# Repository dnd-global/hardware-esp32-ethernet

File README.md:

# Module ESP32 Ethernet UART TTL công nghiệp

Module nối một thiết bị có cổng UART TTL 3,3 V vào mạng. Tín hiệu UART đi qua tầng cách ly 5 kV, rồi ESP32-S3 đưa dữ liệu lên mạng bằng Ethernet hoặc Wi-Fi. Mạch chạy nguồn 9–36 V.

**Tình trạng: Rev B, chưa sản xuất.** Mạch đã đi dây xong, qua kiểm tra luật thiết kế của KiCad và sắp đặt 5 mạch thử. Mọi thứ trong kho này chưa được kiểm chứng trên mạch thật.

| | |
|---|---|
| Kích thước | 80 × 66 mm, 2 lớp, dày 1,6 mm, đồng 1 oz |
| Nguồn vào | 9–36 V qua cọc vít, hạ áp bằng LMR36520 xuống 3,3 V |
| Vi điều khiển | ESP32-S3-WROOM-1-N8, anten mạch in |
| Ethernet | W5500 nối qua SPI, cổng RJ45 HR911105A có sẵn biến áp |
| UART | TTL 3,3 V, cách ly 5 kV bằng CA-IS3642HVW, khe cách ly trên mạch 7,6 mm |
| Đèn báo | LED nguồn và LED trạng thái RGB WS2812B-2020 trên IO38 |
| Linh kiện | 74 linh kiện, 43 loại, lắp một mặt |
| Phần mềm | KiCad 9 |

## Cần góp ý ở đâu

Rất mong nhận góp ý qua mục Issues, nhất là ở bốn chỗ:

1. Mạch hạ áp và lọc đầu vào: vị trí tụ, vòng dòng, tản nhiệt.
2. Đi dây Ethernet trên mạch 2 lớp: hai cặp TX, RX, thạch anh, lớp mass bên dưới.
3. Vùng cách ly: khoảng cách và linh kiện hai phía.
4. Vùng anten của ESP32: vùng cấm đồng, lỗ vít gần anten.

## Trong kho có gì

| Thư mục | Nội dung |
|---|---|
| [`kicad/`](kicad) | Dự án KiCad 9: mạch in, sơ đồ nguyên lý 5 trang, thư viện ký hiệu và footprint |
| [`fab/`](fab) | File đặt sản xuất: Gerber và file khoan, danh sách linh kiện, vị trí linh kiện |
| [`docs/`](docs) | Sơ đồ nguyên lý bản PDF và ảnh |
| [`tools/`](tools) | Bảng nối dây, công cụ sinh sơ đồ và đối chiếu với mạch in, công cụ kiểm tra file lắp ráp |

Mở dự án bằng file `kicad/esp32-eth-uart-module.kicad_pro`. Kho không kèm mô hình 3D của linh kiện nên trình xem 3D của KiCad chỉ hiện bo mạch trống.

## Sơ đồ khối

## Sơ đồ nguyên lý

Bản PDF đủ 5 trang: [`docs/so-do-nguyen-ly.pdf`](docs/so-do-nguyen-ly.pdf). Bấm vào từng ảnh để xem cỡ lớn.

| Trang | Ảnh |
|---|---|
| Nguồn 9–36 V sang 3,3 V |  |
| Vi điều khiển ESP32-S3 |  |
| Ethernet W5500 |  |
| UART TTL cách ly |  |

Mạch này được làm theo thứ tự ngược với thông thường: linh kiện được đặt bằng script từ bảng nối dây [`tools/netlist.py`](tools/netlist.py), đi dây tự động rồi chỉnh tiếp. Sơ đồ nguyên lý được sinh sau, cũng từ bảng đó, để người xem dễ đọc. Vì vậy **file mạch in là bản gốc**. Đừng chạy "Update PCB from Schematic": sáu pad đo mang tên khác nhau ở hai bên (TP1–TP6 trong sơ đồ, 3V3/GND/TXD/RXD/VISO/GISO trên mạch) và footprint trên mạch chưa gắn với ký hiệu trong sơ đồ.

Sơ đồ được đối chiếu tự động với mạch in bằng [`tools/schematic/check_sch.py`](tools/schematic/check_sch.py): 81 linh kiện, 53 đường mạch và 256 chân đều khớp, tên đường mạch cũng trùng. Kiểm tra luật điện (ERC) của KiCad không báo lỗi.

## Mạch in

Vùng sẫm hình chữ L bên phải là khe cách ly. Sáu chấm vàng là pad đo. Hàng lỗ J5 ở mép dưới để trống, dùng khi nạp chương trình.

| Lớp trên | Lớp dưới |
|---|---|
|  |  |

Cận cảnh ba vùng đáng xem kỹ. Trong các ảnh này, đỏ là lớp trên, xanh dương là lớp dưới, chữ trắng là tên đường mạch, nét đứt vàng là vùng cấm đồng.

| Nguồn | Ethernet | Vùng cách ly |
|---|---|---|
|  |  |  |

Ảnh 3D khác: [nhìn chéo phía sau](docs/img/3d-cheo-sau.jpg), [mặt dưới](docs/img/3d-mat-duoi.jpg). Ảnh 3D do KiCad dựng từ mô hình linh kiện, không phải ảnh chụp mạch thật.

## Thông số chế tạo

| | |
|---|---|
| Mạch | 2 lớp, 80 × 66 mm, dày 1,6 mm, đồng 1 oz |
| Đường mạch | nhỏ nhất 0,2 mm, khe hở nhỏ nhất 0,15 mm |
| Via | 0,6 mm, lỗ 0,3 mm, phủ sơn |
| Lỗ bắt vít | 4 lỗ M3 (3,2 mm), không mạ |
| Lắp ráp | 74 linh kiện, một mặt. Cổng RJ45 và cọc vít là loại cắm xuyên lỗ. Hàng chân J5 không lắp. |

File trong `fab/` được chuẩn bị cho dịch vụ lắp ráp của JLCPCB:

- `gateway-s3-revb-gerber.zip`: 9 lớp Gerber và 2 file khoan.
- `gateway-s3-revb-bom.csv`: danh sách linh kiện kèm mã LCSC, mỗi mã một dòng.
- `gateway-s3-revb-cpl.csv`: vị trí và góc đặt linh kiện.

JLCPCB đặt footprint trong thư viện của họ vào vị trí và góc ghi ở file CPL, nên chỗ nào footprint KiCad khác footprint JLCPCB thì file CPL phải bù lại. Ở mạch này có bốn chỗ: U5 xoay −90°, D3 xoay 180°, U4 xoay 270°, J6 lệch 1,41 mm. [`tools/fab/check_cpl.py`](tools/fab/check_cpl.py) kiểm tra việc này cho cả 74 linh kiện: nó đặt footprint của JLCPCB theo từng dòng CPL rồi đo xem mỗi chân rơi cách pad trên mạch bao xa và có đúng chân không.

## Hạn chế đã biết

- Mạch 2 lớp nên hai cặp Ethernet không kiểm soát được trở kháng. Bù lại, đường ngắn dưới 25 mm và không qua via.
- Lớp mass mặt dưới bị một số đường tín hiệu chậm cắt qua, có đoạn nằm dưới W5500.
- Cổng RJ45 chỉ ghi chịu 0–70 °C, cổng USB-C từ −30 đến 80 °C; chưa phải dải nhiệt công nghiệp đầy đủ.
- Vỏ cổng RJ45 nối thẳng mass, không qua tụ 1 nF / 2 kV. Chưa có linh kiện chống tĩnh điện riêng cho cặp Ethernet.
- Đầu cắm UART mượn đầu USB-C nhưng không phải cổng USB: D− là chiều phát ra thiết bị ngoài, D+ là chiều thu về, mức 3,3 V.
- LED trạng thái WS2812B-2020-V6 chạy ở 3,3 V, đúng mép dưới dải cấp 3,3–5,3 V của nó. Độ sáng trong datasheet đo ở 5 V nên trên mạch này có thể thấp hơn.

## Công cụ

Cần KiCad 9 (lệnh `kicad-cli` và module Python `pcbnew`).

```sh
# sinh lại sơ đồ từ bảng nối dây, đối chiếu với mạch in, chạy ERC, xuất PDF và SVG vào tools/schematic/out
cd tools/schematic && ./build.sh

# xuất lại Gerber, danh sách linh kiện và file vị trí vào fab/, rồi kiểm tra file vị trí
cd tools/fab && ./fab.sh && python3 check_cpl.py
```

`check_cpl.py` tải dữ liệu footprint của từng mã LCSC từ thư viện JLCEDA/EasyEDA ở lần chạy đầu và lưu vào `tools/fab/jlc-lib/`.

## Nguồn tham khảo

- Một số footprint trong `kicad/lcsc.pretty` được chuyển từ thư viện chính thức JLCEDA/EasyEDA.
- Mạch đầu cuối Ethernet theo sơ đồ mẫu của WIZnet cho W5500 dùng cổng RJ45 có sẵn biến áp.

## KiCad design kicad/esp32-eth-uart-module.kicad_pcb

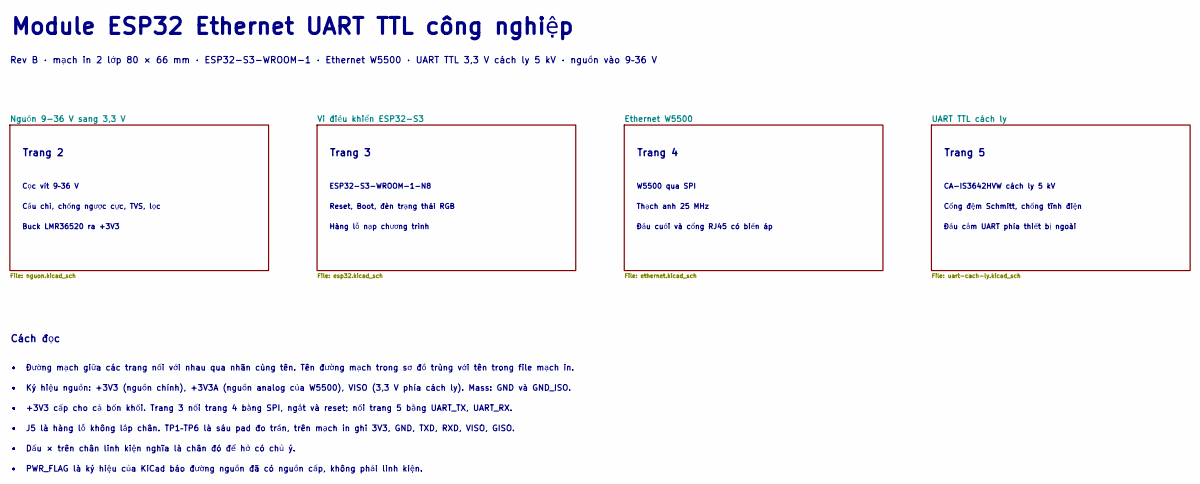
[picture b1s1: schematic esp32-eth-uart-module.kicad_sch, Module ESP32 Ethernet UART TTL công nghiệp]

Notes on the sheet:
Module ESP32 Ethernet UART TTL công nghiệp
Rev B · mạch in 2 lớp 80 × 66 mm · ESP32-S3-WROOM-1 · Ethernet W5500 · UART TTL 3,3 V cách ly 5 kV · nguồn vào 9–36 V
Trang 2
Cọc vít 9–36 V
Cầu chì, chống ngược cực, TVS, lọc
Buck LMR36520 ra +3V3
Trang 3
ESP32-S3-WROOM-1-N8
Reset, Boot, đèn trạng thái RGB
Hàng lỗ nạp chương trình
Trang 4
W5500 qua SPI
Thạch anh 25 MHz
Đầu cuối và cổng RJ45 có biến áp
Trang 5
CA-IS3642HVW cách ly 5 kV
Cổng đệm Schmitt, chống tĩnh điện
Đầu cắm UART phía thiết bị ngoài
Cách đọc
• Đường mạch giữa các trang nối với nhau qua nhãn cùng tên. Tên đường mạch trong sơ đồ trùng với tên trong file mạch in.
• Ký hiệu nguồn: +3V3 (nguồn chính), +3V3A (nguồn analog của W5500), VISO (3,3 V phía cách ly). Mass: GND và GND_ISO.
• +3V3 cấp cho cả bốn khối. Trang 3 nối trang 4 bằng SPI, ngắt và reset; nối trang 5 bằng UART_TX, UART_RX.
• J5 là hàng lỗ không lắp chân. TP1–TP6 là sáu pad đo trần, trên mạch in ghi 3V3, GND, TXD, RXD, VISO, GISO.
• Dấu × trên chân linh kiện nghĩa là chân đó để hở có chủ ý.
• PWR_FLAG là ký hiệu của KiCad báo đường nguồn đã có nguồn cấp, không phải linh kiện.

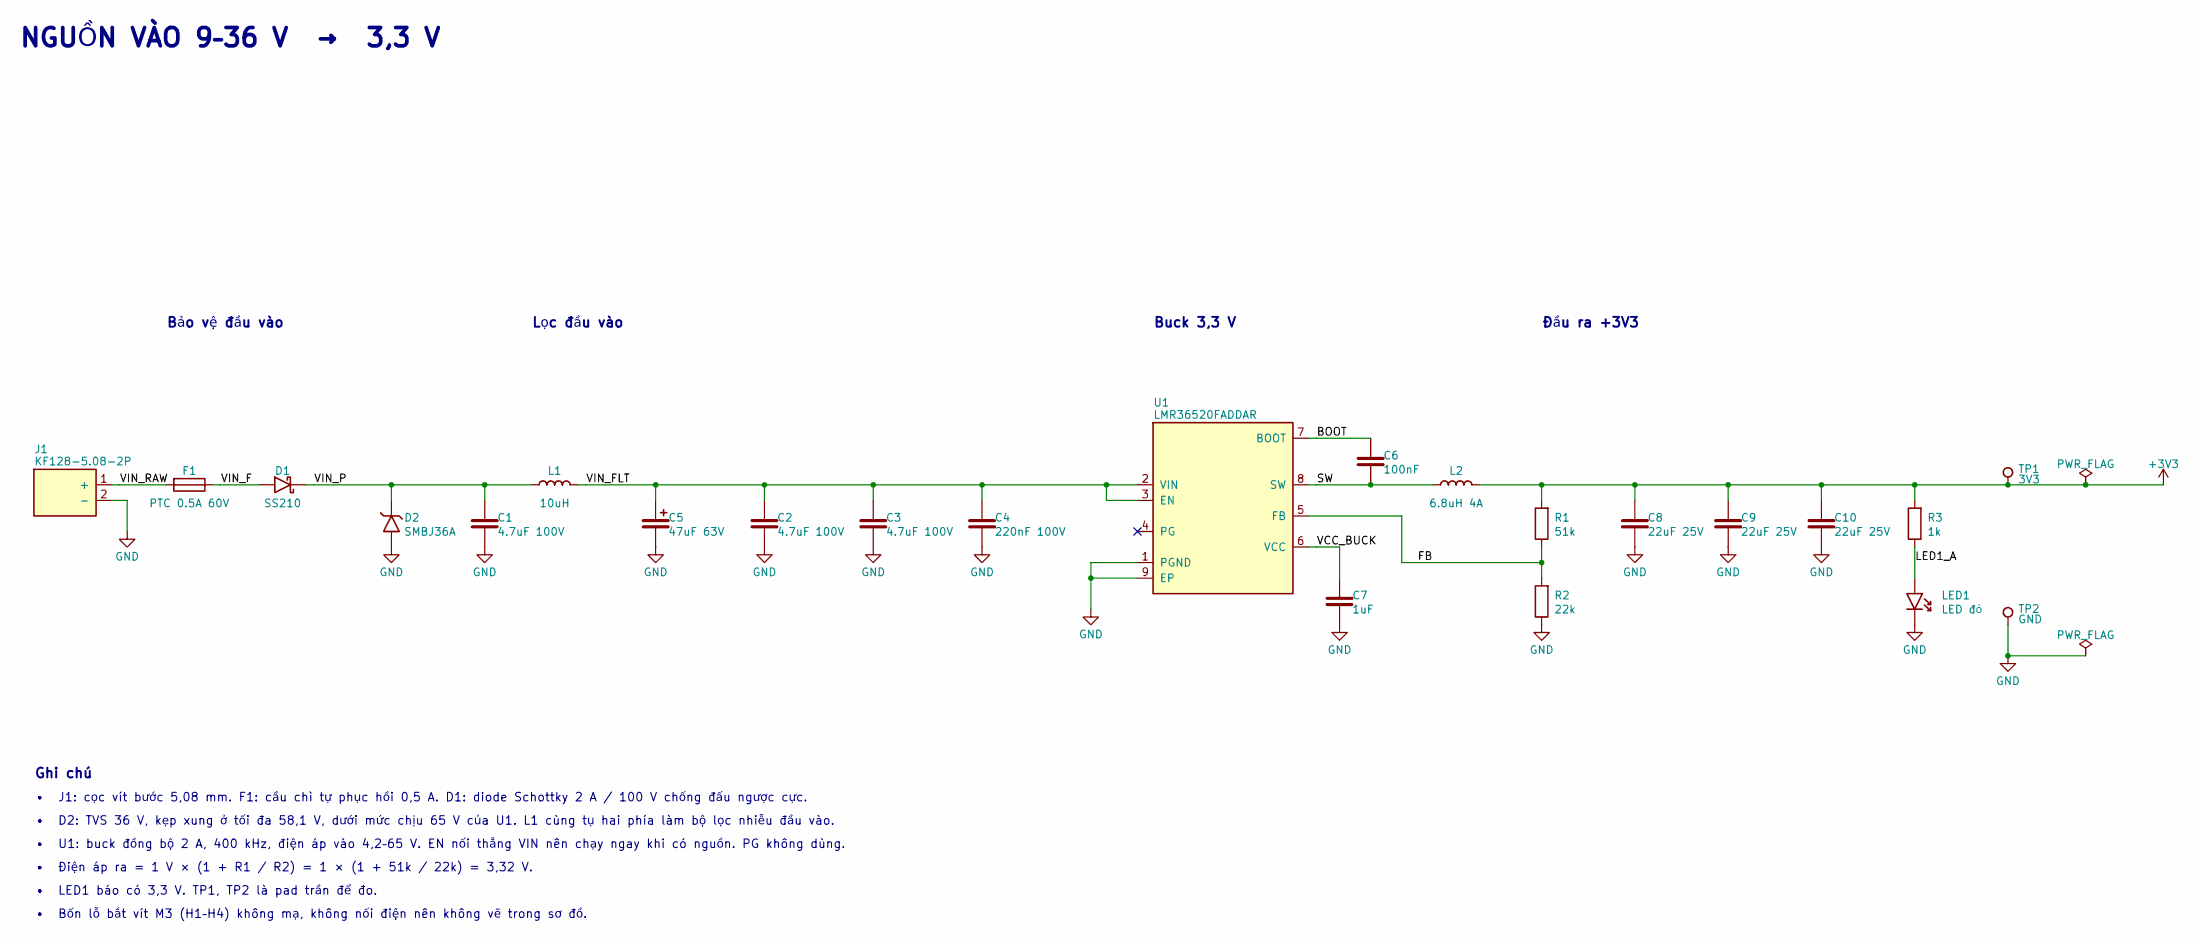
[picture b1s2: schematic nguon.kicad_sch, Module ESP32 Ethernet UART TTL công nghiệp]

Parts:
C1, C2, C3: 4.7uF 100V; C_1210_3225Metric; LCSC C381466
C4: 220nF 100V; C_0603_1608Metric; LCSC C36911431
C5: 47uF 63V; CP_Elec_6.3x7.7; LCSC C48971005
C6: 100nF; C_0603_1608Metric; LCSC C14663
C7: 1uF; C_0603_1608Metric; LCSC C15849
C8, C9, C10: 22uF 25V; C_1206_3216Metric; LCSC C12891
D1: SS210; D_SMA; LCSC C14996
D2: SMBJ36A; D_SMB; LCSC C353364
F1: PTC 0.5A 60V; F1812; LCSC C70113
J1: KF128-5.08-2P; CONN-TH_2P-P5.08_KF128-5.08-2P; LCSC C474952
L1: 10uH; IND-SMD_L4.0-W4.0; LCSC C38117
L2: 6.8uH 4A; IND-SMD_L7.0-W6.6; LCSC C357230
LED1: LED đỏ; LED_0603_1608Metric; LCSC C2286
R1: 51k; R_0603_1608Metric; LCSC C23196
R2: 22k; R_0603_1608Metric; LCSC C31850
R3: 1k; R_0603_1608Metric; LCSC C21190
TP1: 3V3; TestPoint_Pad_D1.5mm
TP2: GND; TestPoint_Pad_D1.5mm
U1: LMR36520FADDAR; POWERPAD-SO-8_L4.9-W3.9-P1.27-LS6.0-BL-EP; LCSC C1858395

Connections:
+3V3: C8.1, C9.1, C10.1, L2.2, R1.1, R3.1, TP1.1; also elsewhere on the board
BOOT: C6.1, U1.7 (BOOT)
FB: R1.2, R2.1, U1.5 (FB)
GND: C1.2, C2.2, C3.2, C4.2, C5.2, C7.2, C8.2, C9.2, C10.2, D2.2, J1.2 (-), LED1.1, R2.2, TP2.1, U1.1 (PGND), U1.9 (EP); also elsewhere on the board
LED1_A: LED1.2, R3.2
PG: U1.4 (PG)
SW: C6.2, L2.1, U1.8 (SW)
VCC_BUCK: C7.1, U1.6 (VCC)
VIN_F: D1.2, F1.1
VIN_FLT: C2.1, C3.1, C4.1, C5.1, L1.2, U1.2 (VIN), U1.3 (EN)
VIN_P: C1.1, D1.1, D2.1, L1.1
VIN_RAW: F1.2, J1.1 (+)

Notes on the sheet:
NGUỒN VÀO 9–36 V → 3,3 V
Bảo vệ đầu vào
Lọc đầu vào
Buck 3,3 V
Đầu ra +3V3
Ghi chú
• J1: cọc vít bước 5,08 mm. F1: cầu chì tự phục hồi 0,5 A. D1: diode Schottky 2 A / 100 V chống đấu ngược cực.
• D2: TVS 36 V, kẹp xung ở tối đa 58,1 V, dưới mức chịu 65 V của U1. L1 cùng tụ hai phía làm bộ lọc nhiễu đầu vào.
• U1: buck đồng bộ 2 A, 400 kHz, điện áp vào 4,2–65 V. EN nối thẳng VIN nên chạy ngay khi có nguồn. PG không dùng.
• Điện áp ra = 1 V × (1 + R1 / R2) = 1 × (1 + 51k / 22k) = 3,32 V.
• LED1 báo có 3,3 V. TP1, TP2 là pad trần để đo.
• Bốn lỗ bắt vít M3 (H1–H4) không mạ, không nối điện nên không vẽ trong sơ đồ.

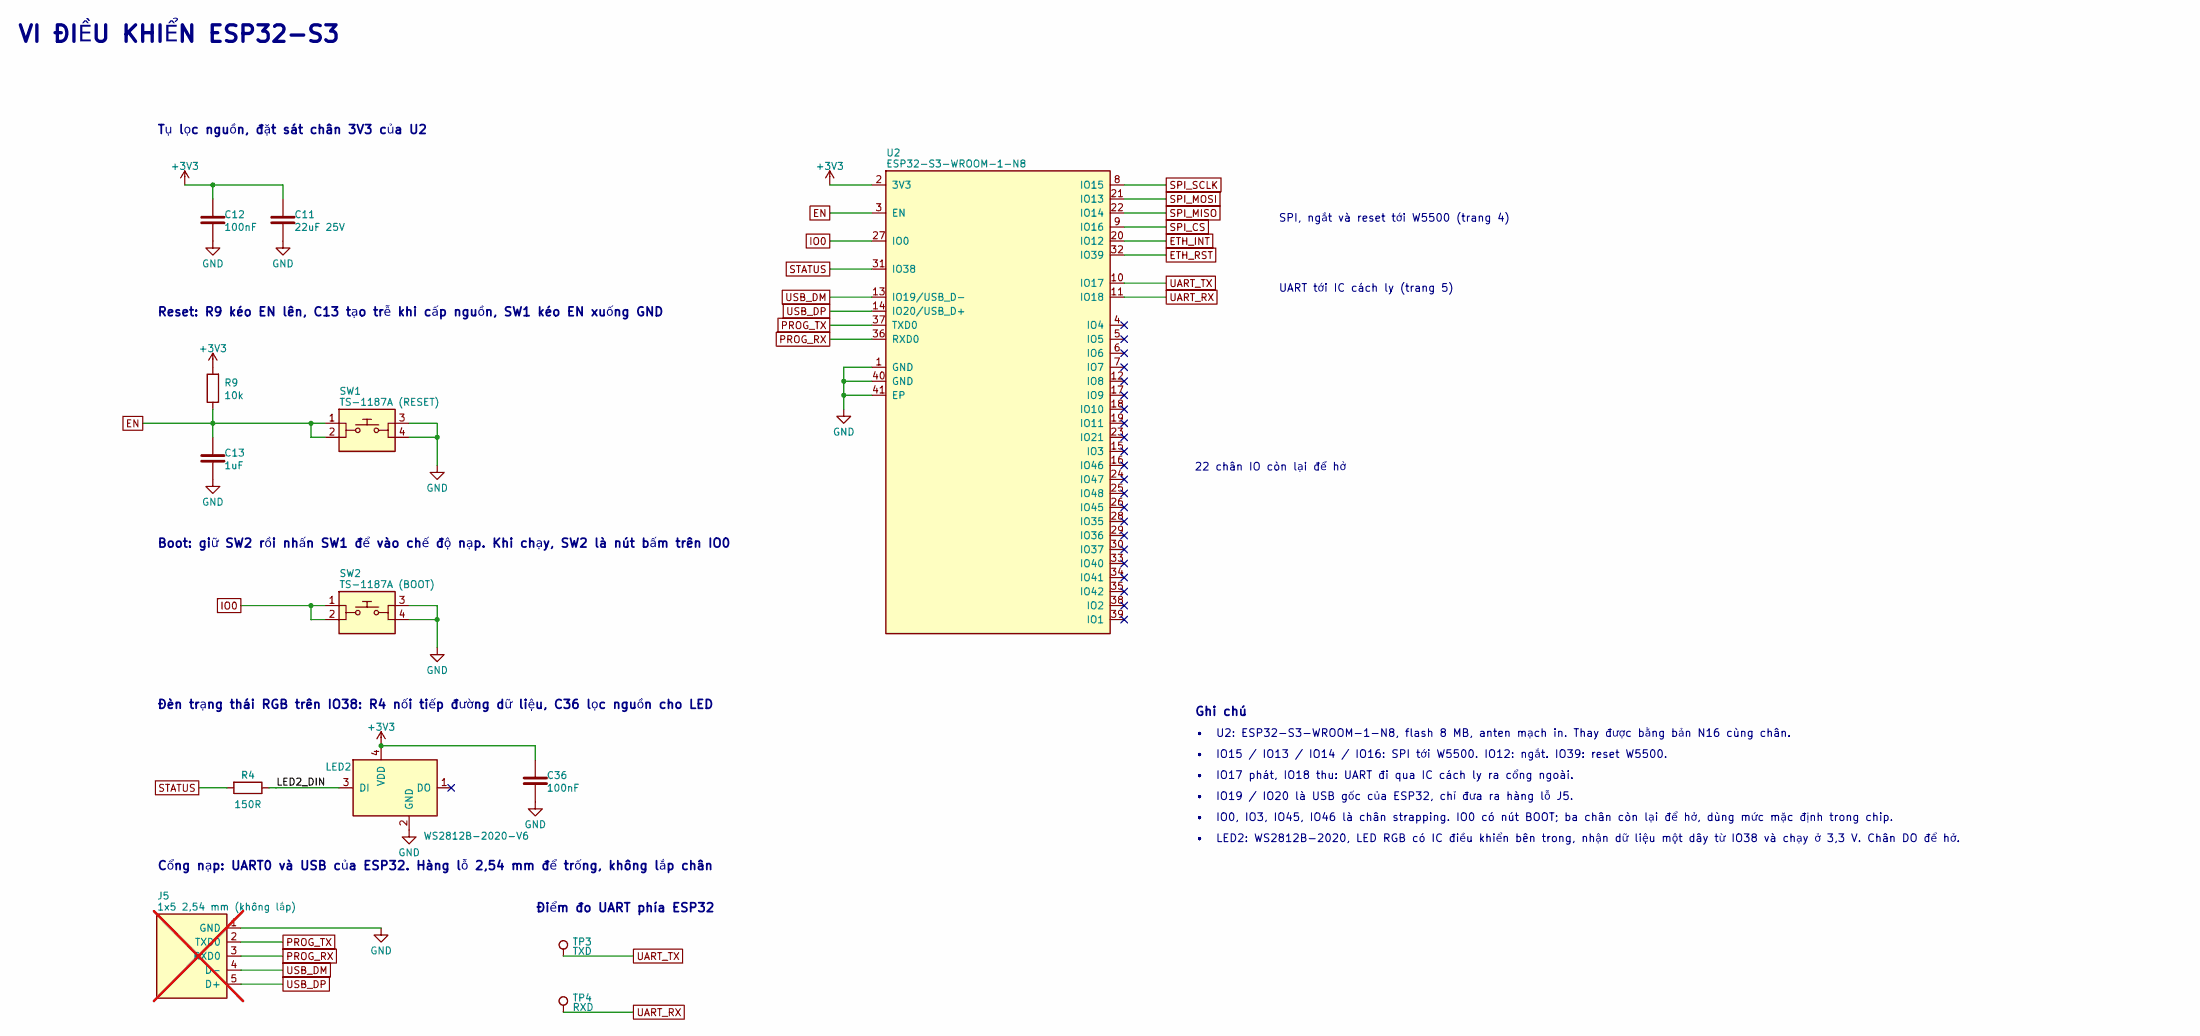
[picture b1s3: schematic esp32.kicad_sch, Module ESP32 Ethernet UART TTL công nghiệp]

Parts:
C11: 22uF 25V; C_1206_3216Metric; LCSC C12891
C12, C36: 100nF; C_0603_1608Metric; LCSC C14663
C13: 1uF; C_0603_1608Metric; LCSC C15849
J5: 1x5 2,54 mm (không lắp); PinHeader_1x05_P2.54mm_Vertical; not fitted
LED2: WS2812B-2020-V6; LED_WS2812B-2020_PLCC4_2.0x2.0mm; LCSC C52917434
R4: 150R; R_0603_1608Metric; LCSC C22808
R9: 10k; R_0603_1608Metric; LCSC C25804
SW1: TS-1187A (RESET); SW-SMD_4P-L5.1-W5.1-P3.70-LS6.5-TL_H1.5; LCSC C318884
SW2: TS-1187A (BOOT); SW-SMD_4P-L5.1-W5.1-P3.70-LS6.5-TL_H1.5; LCSC C318884
TP3: TXD; TestPoint_Pad_D1.5mm
TP4: RXD; TestPoint_Pad_D1.5mm
U2: ESP32-S3-WROOM-1-N8; WIFIM-SMD_ESP32-S3-WROOM-1-N8; LCSC C2913198

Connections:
+3V3: C11.1, C12.1, C36.1, LED2.4 (VDD), R9.1, U2.2 (3V3); also elsewhere on the board
EN: C13.1, R9.2, SW1.1, SW1.2, U2.3 (EN)
ETH_INT: U2.20 (IO12); also elsewhere on the board
ETH_RST: U2.32 (IO39); also elsewhere on the board
GND: C11.2, C12.2, C13.2, C36.2, J5.1 (GND), LED2.2 (GND), SW1.3, SW1.4, SW2.3, SW2.4, U2.1 (GND), U2.40 (GND), U2.41 (EP); also elsewhere on the board
IO0: SW2.1, SW2.2, U2.27 (IO0)
LED2_DIN: LED2.3 (DI), R4.2
PROG_RX: J5.3 (RXD0), U2.36 (RXD0)
PROG_TX: J5.2 (TXD0), U2.37 (TXD0)
SPI_CS: U2.9 (IO16); also elsewhere on the board
SPI_MISO: U2.22 (IO14); also elsewhere on the board
SPI_MOSI: U2.21 (IO13); also elsewhere on the board
SPI_SCLK: U2.8 (IO15); also elsewhere on the board
STATUS: R4.1, U2.31 (IO38)
UART_RX: TP4.1, U2.11 (IO18); also elsewhere on the board
UART_TX: TP3.1, U2.10 (IO17); also elsewhere on the board
USB_DM: J5.4 (D-), U2.13 (IO19/USB_D-)
USB_DP: J5.5 (D+), U2.14 (IO20/USB_D+)

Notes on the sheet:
VI ĐIỀU KHIỂN ESP32-S3
SPI, ngắt và reset tới W5500 (trang 4)
UART tới IC cách ly (trang 5)
22 chân IO còn lại để hở
Tụ lọc nguồn, đặt sát chân 3V3 của U2
Reset: R9 kéo EN lên, C13 tạo trễ khi cấp nguồn, SW1 kéo EN xuống GND
Boot: giữ SW2 rồi nhấn SW1 để vào chế độ nạp. Khi chạy, SW2 là nút bấm trên IO0
Đèn trạng thái RGB trên IO38: R4 nối tiếp đường dữ liệu, C36 lọc nguồn cho LED
Cổng nạp: UART0 và USB của ESP32. Hàng lỗ 2,54 mm để trống, không lắp chân
Điểm đo UART phía ESP32
Ghi chú
• U2: ESP32-S3-WROOM-1-N8, flash 8 MB, anten mạch in. Thay được bằng bản N16 cùng chân.
• IO15 / IO13 / IO14 / IO16: SPI tới W5500. IO12: ngắt. IO39: reset W5500.
• IO17 phát, IO18 thu: UART đi qua IC cách ly ra cổng ngoài.
• IO19 / IO20 là USB gốc của ESP32, chỉ đưa ra hàng lỗ J5.
• IO0, IO3, IO45, IO46 là chân strapping. IO0 có nút BOOT; ba chân còn lại để hở, dùng mức mặc định trong chip.
• LED2: WS2812B-2020, LED RGB có IC điều khiển bên trong, nhận dữ liệu một dây từ IO38 và chạy ở 3,3 V. Chân DO để hở.

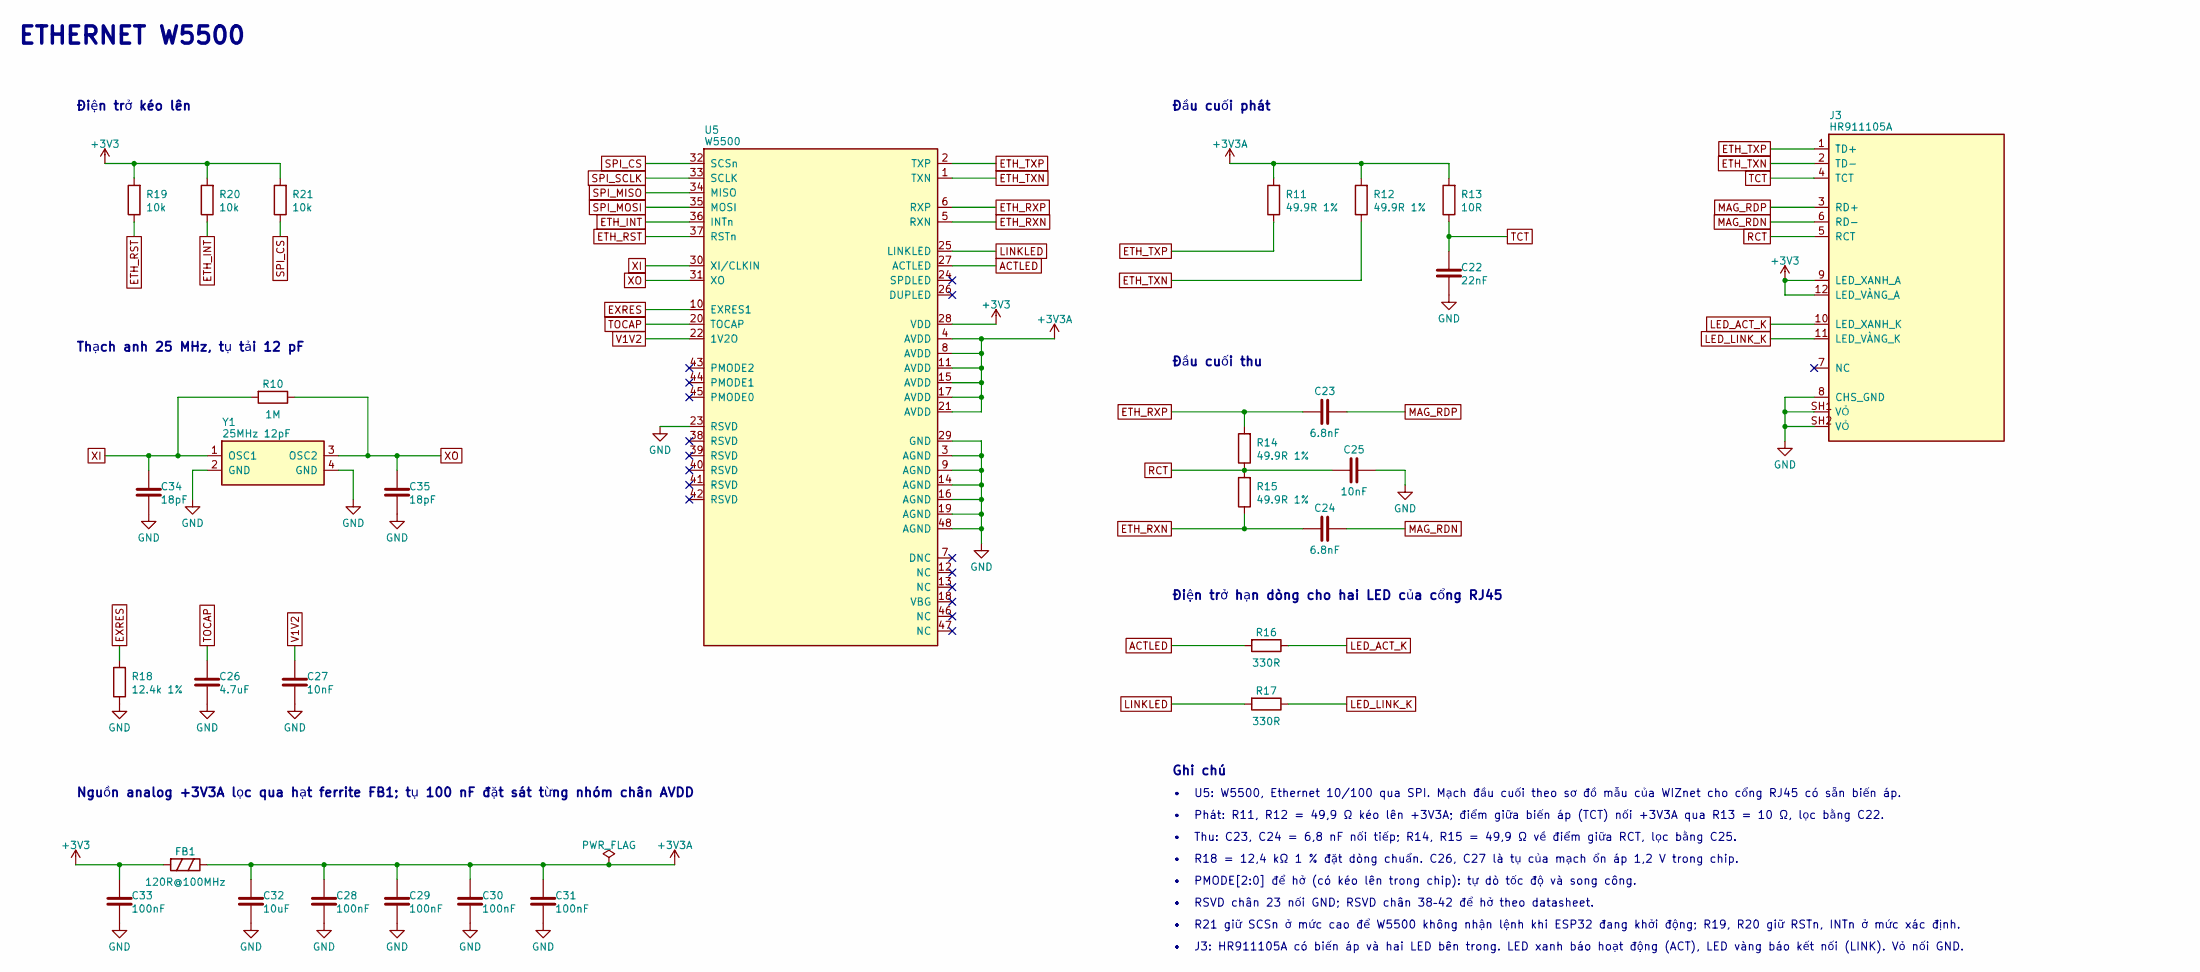
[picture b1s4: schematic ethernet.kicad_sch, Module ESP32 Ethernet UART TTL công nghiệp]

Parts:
C22: 22nF; C_0603_1608Metric; LCSC C21122
C23, C24: 6.8nF; C_0603_1608Metric; LCSC C1631
C25, C27: 10nF; C_0603_1608Metric; LCSC C57112
C26: 4.7uF; C_0603_1608Metric; LCSC C19666
C28, C29, C30, C31, C33: 100nF; C_0603_1608Metric; LCSC C14663
C32: 10uF; C_0805_2012Metric; LCSC C15850
C34, C35: 18pF; C_0603_1608Metric; LCSC C1647
FB1: 120R@100MHz; L_0603_1608Metric; LCSC C14709
J3: HR911105A; RJ45-TH_HR911105A; LCSC C12074
R10: 1M; R_0603_1608Metric; LCSC C22935
R11, R12, R14, R15: 49.9R 1%; R_0603_1608Metric; LCSC C23185
R13: 10R; R_0603_1608Metric; LCSC C22859
R16, R17: 330R; R_0603_1608Metric; LCSC C23138
R18: 12.4k 1%; R_0603_1608Metric; LCSC C2930060
R19, R20, R21: 10k; R_0603_1608Metric; LCSC C25804
U5: W5500; LQFP-48_7x7mm_P0.5mm; LCSC C32843
Y1: 25MHz 12pF; Crystal_SMD_3225-4Pin_3.2x2.5mm; LCSC C9006

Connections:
+3V3: C33.1, FB1.1, J3.9 (LED_XANH_A), J3.12 (LED_VÀNG_A), R19.1, R20.1, R21.1, U5.28 (VDD); also elsewhere on the board
+3V3A: C28.1, C29.1, C30.1, C31.1, C32.1, FB1.2, R11.1, R12.1, R13.1, U5.4 (AVDD), U5.8 (AVDD), U5.11 (AVDD), U5.15 (AVDD), U5.17 (AVDD), U5.21 (AVDD)
ACTLED: R16.2, U5.27 (ACTLED)
ETH_INT: R20.2, U5.36 (INTn); also elsewhere on the board
ETH_RST: R19.2, U5.37 (RSTn); also elsewhere on the board
ETH_RXN: C24.1, R15.1, U5.5 (RXN)
ETH_RXP: C23.1, R14.1, U5.6 (RXP)
ETH_TXN: J3.2 (TD-), R12.2, U5.1 (TXN)
ETH_TXP: J3.1 (TD+), R11.2, U5.2 (TXP)
EXRES: R18.1, U5.10 (EXRES1)
GND: C22.2, C25.2, C26.2, C27.2, C28.2, C29.2, C30.2, C31.2, C32.2, C33.2, C34.2, C35.2, J3.8 (CHS_GND), J3.SH1 (VỎ), J3.SH2 (VỎ), R18.2, U5.3 (AGND), U5.9 (AGND), U5.14 (AGND), U5.16 (AGND), U5.19 (AGND), U5.23 (RSVD), U5.29 (GND), U5.48 (AGND), Y1.2 (GND), Y1.4 (GND); also elsewhere on the board
LED_ACT_K: J3.10 (LED_XANH_K), R16.1
LED_LINK_K: J3.11 (LED_VÀNG_K), R17.1
LINKLED: R17.2, U5.25 (LINKLED)
MAG_RDN: C24.2, J3.6 (RD-)
MAG_RDP: C23.2, J3.3 (RD+)
RCT: C25.1, J3.5 (RCT), R14.2, R15.2
SPI_CS: R21.2, U5.32 (SCSn); also elsewhere on the board
SPI_MISO: U5.34 (MISO); also elsewhere on the board
SPI_MOSI: U5.35 (MOSI); also elsewhere on the board
SPI_SCLK: U5.33 (SCLK); also elsewhere on the board
TCT: C22.1, J3.4 (TCT), R13.2
TOCAP: C26.1, U5.20 (TOCAP)
V1V2: C27.1, U5.22 (1V2O)
XI: C34.1, R10.1, U5.30 (XI/CLKIN), Y1.1 (OSC1)
XO: C35.1, R10.2, U5.31 (XO), Y1.3 (OSC2)

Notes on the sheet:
ETHERNET W5500
Điện trở kéo lên
Thạch anh 25 MHz, tụ tải 12 pF
Nguồn analog +3V3A lọc qua hạt ferrite FB1; tụ 100 nF đặt sát từng nhóm chân AVDD
Đầu cuối phát
Đầu cuối thu
Điện trở hạn dòng cho hai LED của cổng RJ45
Ghi chú
• U5: W5500, Ethernet 10/100 qua SPI. Mạch đầu cuối theo sơ đồ mẫu của WIZnet cho cổng RJ45 có sẵn biến áp.
• Phát: R11, R12 = 49,9 Ω kéo lên +3V3A; điểm giữa biến áp (TCT) nối +3V3A qua R13 = 10 Ω, lọc bằng C22.
• Thu: C23, C24 = 6,8 nF nối tiếp; R14, R15 = 49,9 Ω về điểm giữa RCT, lọc bằng C25.
• R18 = 12,4 kΩ 1 % đặt dòng chuẩn. C26, C27 là tụ của mạch ổn áp 1,2 V trong chip.
• PMODE[2:0] để hở (có kéo lên trong chip): tự dò tốc độ và song công.
• RSVD chân 23 nối GND; RSVD chân 38–42 để hở theo datasheet.
• R21 giữ SCSn ở mức cao để W5500 không nhận lệnh khi ESP32 đang khởi động; R19, R20 giữ RSTn, INTn ở mức xác định.
• J3: HR911105A có biến áp và hai LED bên trong. LED xanh báo hoạt động (ACT), LED vàng báo kết nối (LINK). Vỏ nối GND.

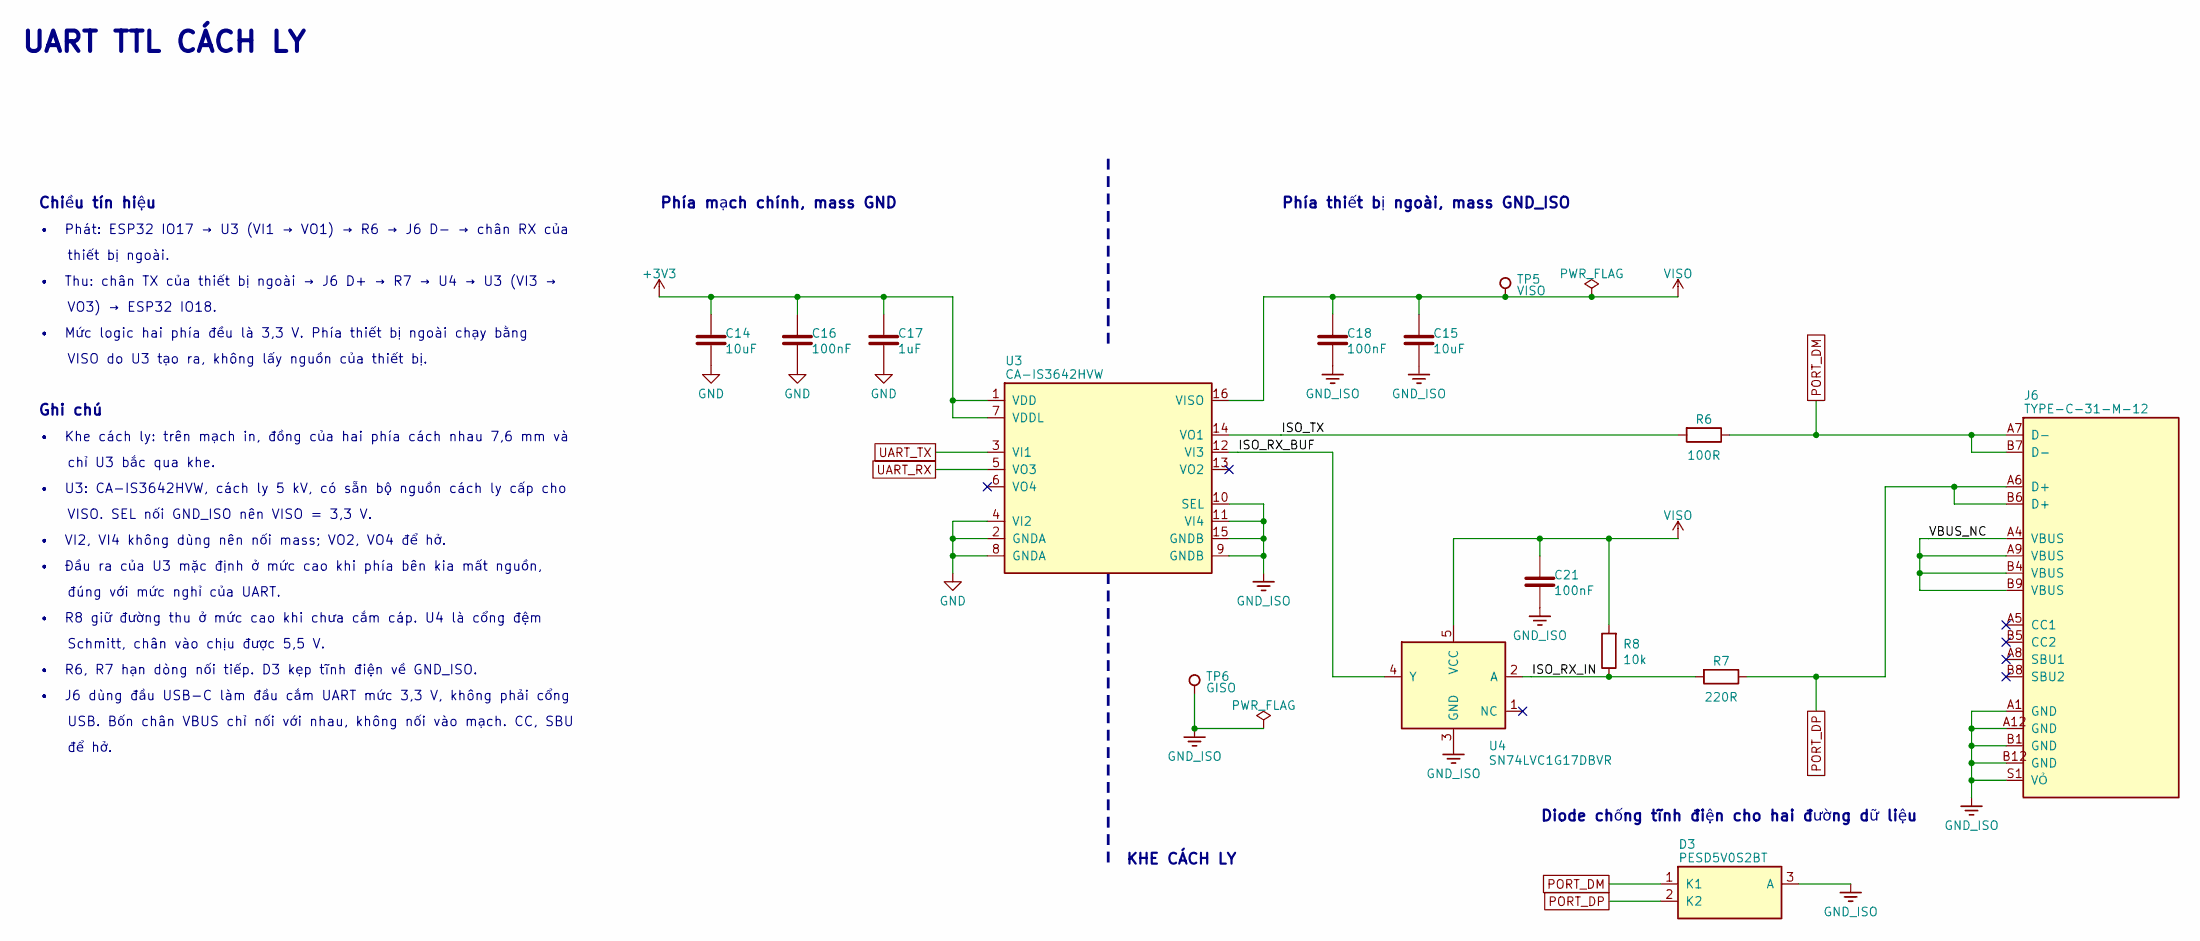
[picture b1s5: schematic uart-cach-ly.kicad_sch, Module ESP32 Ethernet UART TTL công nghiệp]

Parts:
C14, C15: 10uF; C_0805_2012Metric; LCSC C15850
C16, C18, C21: 100nF; C_0603_1608Metric; LCSC C14663
C17: 1uF; C_0603_1608Metric; LCSC C15849
D3: PESD5V0S2BT; SOT-23; LCSC C49338
J6: TYPE-C-31-M-12; USB_C_Receptacle_HRO_TYPE-C-31-M-12; LCSC C165948
R6: 100R; R_0603_1608Metric; LCSC C22775
R7: 220R; R_0603_1608Metric; LCSC C22962
R8: 10k; R_0603_1608Metric; LCSC C25804
TP5: VISO; TestPoint_Pad_D1.5mm
TP6: GISO; TestPoint_Pad_D1.5mm
U3: CA-IS3642HVW; SOIC-16_L10.3-W7.5-P1.27-LS10.3-TL; LCSC C5440874
U4: SN74LVC1G17DBVR; SOT-25-5_L3.0-W1.8-P0.95-LS3.0-BL; LCSC C7836

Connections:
+3V3: C14.1, C16.1, C17.1, U3.1 (VDD), U3.7 (VDDL); also elsewhere on the board
GND: C14.2, C16.2, C17.2, U3.2 (GNDA), U3.4 (VI2), U3.8 (GNDA); also elsewhere on the board
GND_ISO: C15.2, C18.2, C21.2, D3.3 (A), J6.A1 (GND), J6.A12 (GND), J6.B1 (GND), J6.B12 (GND), J6.S1 (VỎ), TP6.1, U3.9 (GNDB), U3.10 (SEL), U3.11 (VI4), U3.15 (GNDB), U4.3 (GND); also elsewhere on the board
ISO_RX_BUF: U3.12 (VI3), U4.4 (Y)
ISO_RX_IN: R7.2, R8.2, U4.2 (A)
ISO_TX: R6.1, U3.14 (VO1)
PORT_DM: D3.1 (K1), J6.A7 (D-), J6.B7 (D-), R6.2
PORT_DP: D3.2 (K2), J6.A6 (D+), J6.B6 (D+), R7.1
UART_RX: U3.5 (VO3); also elsewhere on the board
UART_TX: U3.3 (VI1); also elsewhere on the board
VBUS_NC: J6.A4 (VBUS), J6.A9 (VBUS), J6.B4 (VBUS), J6.B9 (VBUS)
VISO: C15.1, C18.1, C21.1, R8.1, TP5.1, U3.16 (VISO), U4.5 (VCC); also elsewhere on the board

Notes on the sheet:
UART TTL CÁCH LY
Diode chống tĩnh điện cho hai đường dữ liệu
KHE CÁCH LY
Phía mạch chính, mass GND
Phía thiết bị ngoài, mass GND_ISO
Chiều tín hiệu
• Phát: ESP32 IO17 → U3 (VI1 → VO1) → R6 → J6 D− → chân RX của
thiết bị ngoài.
• Thu: chân TX của thiết bị ngoài → J6 D+ → R7 → U4 → U3 (VI3 →
VO3) → ESP32 IO18.
• Mức logic hai phía đều là 3,3 V. Phía thiết bị ngoài chạy bằng
VISO do U3 tạo ra, không lấy nguồn của thiết bị.
Ghi chú
• Khe cách ly: trên mạch in, đồng của hai phía cách nhau 7,6 mm và
chỉ U3 bắc qua khe.
• U3: CA-IS3642HVW, cách ly 5 kV, có sẵn bộ nguồn cách ly cấp cho
VISO. SEL nối GND_ISO nên VISO = 3,3 V.
• VI2, VI4 không dùng nên nối mass; VO2, VO4 để hở.
• Đầu ra của U3 mặc định ở mức cao khi phía bên kia mất nguồn,
đúng với mức nghỉ của UART.
• R8 giữ đường thu ở mức cao khi chưa cắm cáp. U4 là cổng đệm
Schmitt, chân vào chịu được 5,5 V.
• R6, R7 hạn dòng nối tiếp. D3 kẹp tĩnh điện về GND_ISO.
• J6 dùng đầu USB-C làm đầu cắm UART mức 3,3 V, không phải cổng
USB. Bốn chân VBUS chỉ nối với nhau, không nối vào mạch. CC, SBU
để hở.

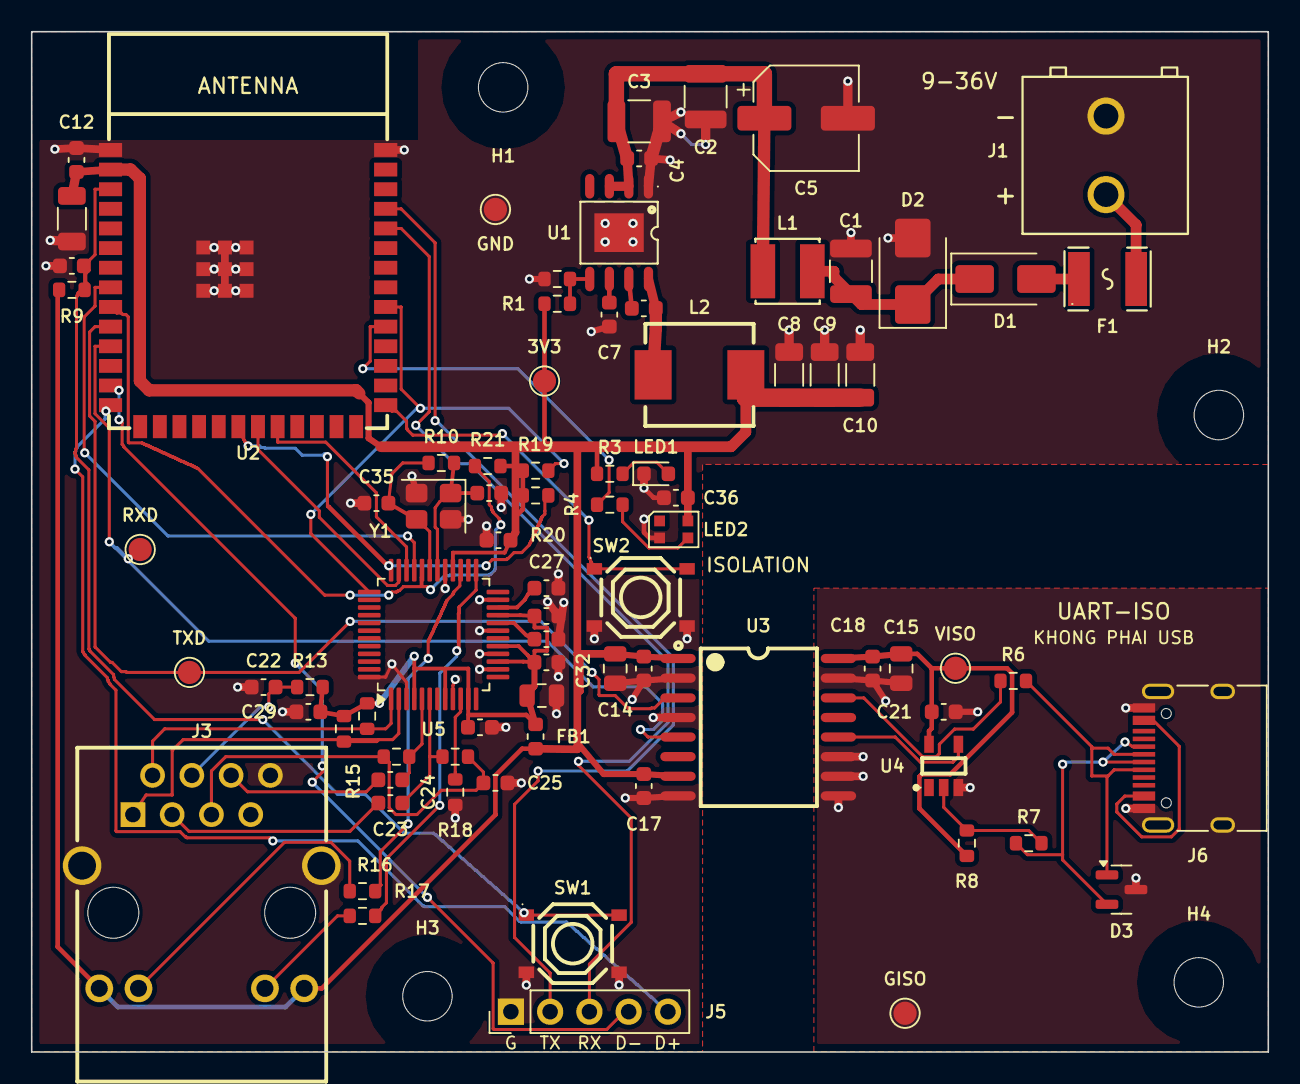
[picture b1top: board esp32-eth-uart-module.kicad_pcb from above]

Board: 2 copper layers, 80.0 x 66.0 mm, 85 parts (0 on the bottom side), 53 nets.

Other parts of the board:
3V3: test point +3V3; TestPoint_Pad_D1.5mm
GISO: test point GND_ISO; TestPoint_Pad_D1.5mm
GND: test point GND; TestPoint_Pad_D1.5mm
H1, H2, H3, H4: MountingHole_3.2mm_M3
RXD: test point UART_RX; TestPoint_Pad_D1.5mm
TXD: test point UART_TX; TestPoint_Pad_D1.5mm
VISO: test point VISO; TestPoint_Pad_D1.5mm

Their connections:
+3V3: 3V3.1; also elsewhere on the board
GND: GND.1; also elsewhere on the board
GND_ISO: GISO.1; also elsewhere on the board
UART_RX: RXD.1; also elsewhere on the board
UART_TX: TXD.1; also elsewhere on the board
VISO: VISO.1; also elsewhere on the board

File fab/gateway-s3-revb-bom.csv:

Comment,Designator,Footprint,LCSC Part #
4.7uF 100V,"C1,C2,C3",C_1210_3225Metric,C381466
22nF,C22,C_0603_1608Metric,C21122
6.8nF,"C23,C24",C_0603_1608Metric,C1631
4.7uF,C26,C_0603_1608Metric,C19666
10nF,"C27,C25",C_0603_1608Metric,C57112
10uF,"C32,C14,C15",C_0805_2012Metric,C15850
18pF,"C34,C35",C_0603_1608Metric,C1647
220nF 100V,C4,C_0603_1608Metric,C36911431
47uF 63V,C5,CP_Elec_6.3x7.7,C48971005
100nF,"C6,C12,C36,C28,C29,C30,C31,C33,C16,C18,C21",C_0603_1608Metric,C14663
1uF,"C7,C13,C17",C_0603_1608Metric,C15849
22uF 25V,"C8,C9,C10,C11",C_1206_3216Metric,C12891
SS210,D1,D_SMA,C14996
SMBJ36A,D2,D_SMB,C353364
PESD5V0S2BT,D3,SOT-23,C49338
PTC 0.5A 60V,F1,F1812,C70113
120R@100MHz,FB1,L_0603_1608Metric,C14709
KF128-5.08-2P (+ / -),J1,CONN-TH_2P-P5.08_KF128-5.08-2P,C474952
HR911105A,J3,RJ45-TH_HR911105A,C12074
UART-ISO,J6,USB_C_Receptacle_HRO_TYPE-C-31-M-12,C165948
10uH,L1,IND-SMD_L4.0-W4.0,C38117
6.8uH 4A,L2,IND-SMD_L7.0-W6.6,C357230
PWR red,LED1,LED_0603_1608Metric,C2286
WS2812B-2020-V6,LED2,LED_WS2812B-2020_PLCC4_2.0x2.0mm,C52917434
51k,R1,R_0603_1608Metric,C23196
1M,R10,R_0603_1608Metric,C22935
49.9R 1%,"R11,R12,R14,R15",R_0603_1608Metric,C23185
10R,R13,R_0603_1608Metric,C22859
330R,"R16,R17",R_0603_1608Metric,C23138
12.4k 1%,R18,R_0603_1608Metric,C2930060
22k,R2,R_0603_1608Metric,C31850
1k,R3,R_0603_1608Metric,C21190
150R,R4,R_0603_1608Metric,C22808
100R,R6,R_0603_1608Metric,C22775
220R,R7,R_0603_1608Metric,C22962
10k,"R9,R19,R20,R21,R8",R_0603_1608Metric,C25804
RESET / BOOT,"SW1,SW2",SW-SMD_4P-L5.1-W5.1-P3.70-LS6.5-TL_H1.5,C318884
LMR36520,U1,POWERPAD-SO-8_L4.9-W3.9-P1.27-LS6.0-BL-EP,C1858395
ESP32-S3-WROOM-1-N8,U2,WIFIM-SMD_ESP32-S3-WROOM-1-N8,C2913198
CA-IS3642HVW,U3,SOIC-16_L10.3-W7.5-P1.27-LS10.3-TL,C5440874
SN74LVC1G17DBVR,U4,SOT-25-5_L3.0-W1.8-P0.95-LS3.0-BL,C7836
W5500,U5,LQFP-48_7x7mm_P0.5mm,C32843
25MHz 12pF,Y1,Crystal_SMD_3225-4Pin_3.2x2.5mm,C9006

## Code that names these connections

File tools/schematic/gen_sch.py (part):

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
    s.box("J1", "KF128_2P", [], [("1", "+"), ("2", "-")], 10.16, 22.86, Y(-2.54), prefix="J")
    DONE.update({("J1", "1"), ("J1", "2")})
    s.w(("J1", "1"), (44.45, R)); s.llabel("VIN_RAW", (36.83, R))
    s.w(("J1", "2"), (38.1, Y(2.54)), (38.1, Y(7.62))); s.term((38.1, Y(7.62)), "GND")
    p = s.hpart("F1", 44.45, R, "VIN_RAW")
    s.w(p, (59.69, R)); s.llabel("VIN_F", (53.34, R))
    p = s.hpart("D1", 59.69, R, "VIN_F")
    s.w(p, (81.28, R), (96.52, R), (104.14, R)); s.llabel("VIN_P", (68.58, R))
    s.down(81.28, R, ["D2"], "VIN_P")
    s.down(96.52, R, ["C1"], "VIN_P")
    p = s.hpart("L1", 104.14, R, "VIN_P")
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    right = [("7", "BOOT"), None, None, ("8", "SW"), None, ("5", "FB"), None, ("6", "VCC")]
    s.box("U1", "LMR36520", left, right, 22.86, 205.74, Y(-10.16))
    caps = [124.46, 142.24, 160.02, 177.8]
    s.w(p, *[(x, R) for x in caps], (198.12, R), ("U1", "2")); s.llabel("VIN_FLT", (113.03, R))
    for x, ref in zip(caps, ["C5", "C2", "C3", "C4"]):
        s.down(x, R, [ref], "VIN_FLT")
    s.w(("U1", "3"), (198.12, Y(2.54)), (198.12, R))
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    s.w((231.14, 43.18), (238.76, 43.18), (254.0, 43.18), (269.24, 43.18)); s.term((231.14, 43.18), "+3V3A")
    for x, ref in ((238.76, "R11"), (254.0, "R12"), (269.24, "R13")):
        s.w((x, 43.18), (x, 45.72)); s.vpart(ref, x, 45.72, "+3V3A")
    s.w((220.98, 58.42), (238.76, 58.42), (238.76, 53.34)); s.glabel("ETH_TXP", (220.98, 58.42), "L")
    s.w((220.98, 63.5), (254.0, 63.5), (254.0, 53.34)); s.glabel("ETH_TXN", (220.98, 63.5), "L")
    s.w((269.24, 53.34), (269.24, 55.88), (269.24, 58.42)); s.w((269.24, 55.88), (279.4, 55.88)); s.glabel("TCT", (279.4, 55.88), "R")
    b = s.vpart("C22", 269.24, 58.42, "TCT"); s.term(b, "GND")
    s.sub("Đầu cuối phát", 220.98, 34.29)
    # RX termination
    y1, yr, y2 = 86.36, 96.52, 106.68
    s.glabel("ETH_RXP", (220.98, y1), "L"); s.w((220.98, y1), (233.68, y1), (243.84, y1))
    p = s.hpart("C23", 243.84, y1, "ETH_RXP"); s.w(p, (261.62, y1)); s.glabel("MAG_RDP", (261.62, y1), "R")
    s.w((233.68, y1), (233.68, y1 + 2.54)); s.vpart("R14", 233.68, y1 + 2.54, "ETH_RXP")
    b = s.vpart("R15", 233.68, yr, "RCT"); s.w(b, (233.68, y2))
    s.glabel("ETH_RXN", (220.98, y2), "L"); s.w((220.98, y2), (233.68, y2), (243.84, y2))
    p = s.hpart("C24", 243.84, y2, "ETH_RXN"); s.w(p, (261.62, y2)); s.glabel("MAG_RDN", (261.62, y2), "R")
    s.glabel("RCT", (220.98, yr), "L"); s.w((220.98, yr), (233.68, yr), (248.92, yr))
    p = s.hpart("C25", 248.92, yr, "RCT"); s.w(p, (261.62, yr), (261.62, yr + 2.54)); s.term((261.62, yr + 2.54), "GND")
    s.sub("Đầu cuối thu", 220.98, 78.74)
    # LED resistors
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    s.bus("U3", ["10", "11", "15", "9"], 5.08)
    s.stub("U3", "13")
    # transmit path: isolator -> R6 -> connector D-
    s.w(("U3", "14"), (264.16, 78.74)); s.llabel("ISO_TX", (205.74, 78.74))
    p = s.hpart("R6", 264.16, 78.74, "ISO_TX")
    DONE.add(("U3", "14"))
    jl = [("A7", "D-"), ("B7", "D-"), None, ("A6", "D+"), ("B6", "D+"), None, ("A4", "VBUS"), ("A9", "VBUS"), ("B4", "VBUS"),
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    s.box("J6", "USB-C_16P", jl, [], 22.86, 314.96, 76.2, prefix="J")
    s.w(p, (284.48, 78.74), (307.34, 78.74), ("J6", "A7"))
    s.w(("J6", "B7"), (307.34, 81.28), (307.34, 78.74))
    s.w((284.48, 78.74), (284.48, 73.66)); s.glabel("PORT_DM", (284.48, 73.66), "U")
    # receive path: connector D+ -> R7 -> Schmitt buffer U4 -> isolator
    s.box("U4", "SN74LVC1G17", [None, ("4", "Y"), None, None], [None, ("2", "A"), None, ("1", "NC")], 15.24, 223.52, 109.22,
          top=[("5", "VCC", 7.62)], bottom=[("3", "GND", 7.62)], ref_at=(236.22, 124.46, "left"), val_at=(236.22, 126.6, "left"))
    s.w(("U3", "12"), (213.36, 81.28), (213.36, 114.3), ("U4", "4")); s.llabel("ISO_RX_BUF", (199.39, 81.28))
    s.w(("U4", "5"), (231.14, 93.98), (243.84, 93.98), (254.0, 93.98), (264.16, 93.98)); s.term((264.16, 93.98), "VISO")
    s.down(243.84, 93.98, ["C21"], "VISO")
    s.w((254.0, 93.98), (254.0, 106.68)); s.vpart("R8", 254.0, 106.68, "VISO")
    s.w(("U4", "2"), (254.0, 114.3), (266.7, 114.3)); s.llabel("ISO_RX_IN", (242.57, 114.3))
    q = s.hpart("R7", 266.7, 114.3, "ISO_RX_IN")
    s.term(s.P("U4", "3"), "GND_ISO")
    s.nc(s.P("U4", "1"))
    DONE.update({("U3", "12"), ("U4", "1"), ("U4", "2"), ("U4", "3"), ("U4", "4"), ("U4", "5")})
    s.w(q, (284.48, 114.3), (294.64, 114.3), (294.64, 86.36), (304.8, 86.36), ("J6", "A6"))
    s.w(("J6", "B6"), (304.8, 88.9), (304.8, 86.36))
    s.w((284.48, 114.3), (284.48, 119.38)); s.glabel("PORT_DP", (284.48, 119.38), "D")
    DONE.update({("J6", k) for k in ("A7", "B7", "A6", "B6")})
    for k in ("A4", "A9", "B4", "B9"):
        s.w(("J6", k), (299.72, s.P("J6", k)[1])); DONE.add(("J6", k))
    s.w((299.72, s.P("J6", "A4")[1]), (299.72, s.P("J6", "B9")[1])); s.llabel("VBUS_NC", (300.99, s.P("J6", "A4")[1]))
    s.bus("J6", ["A1", "A12", "B1", "B12", "S1"], -5.08)
    s.auto("J6")
    # ESD diode
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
